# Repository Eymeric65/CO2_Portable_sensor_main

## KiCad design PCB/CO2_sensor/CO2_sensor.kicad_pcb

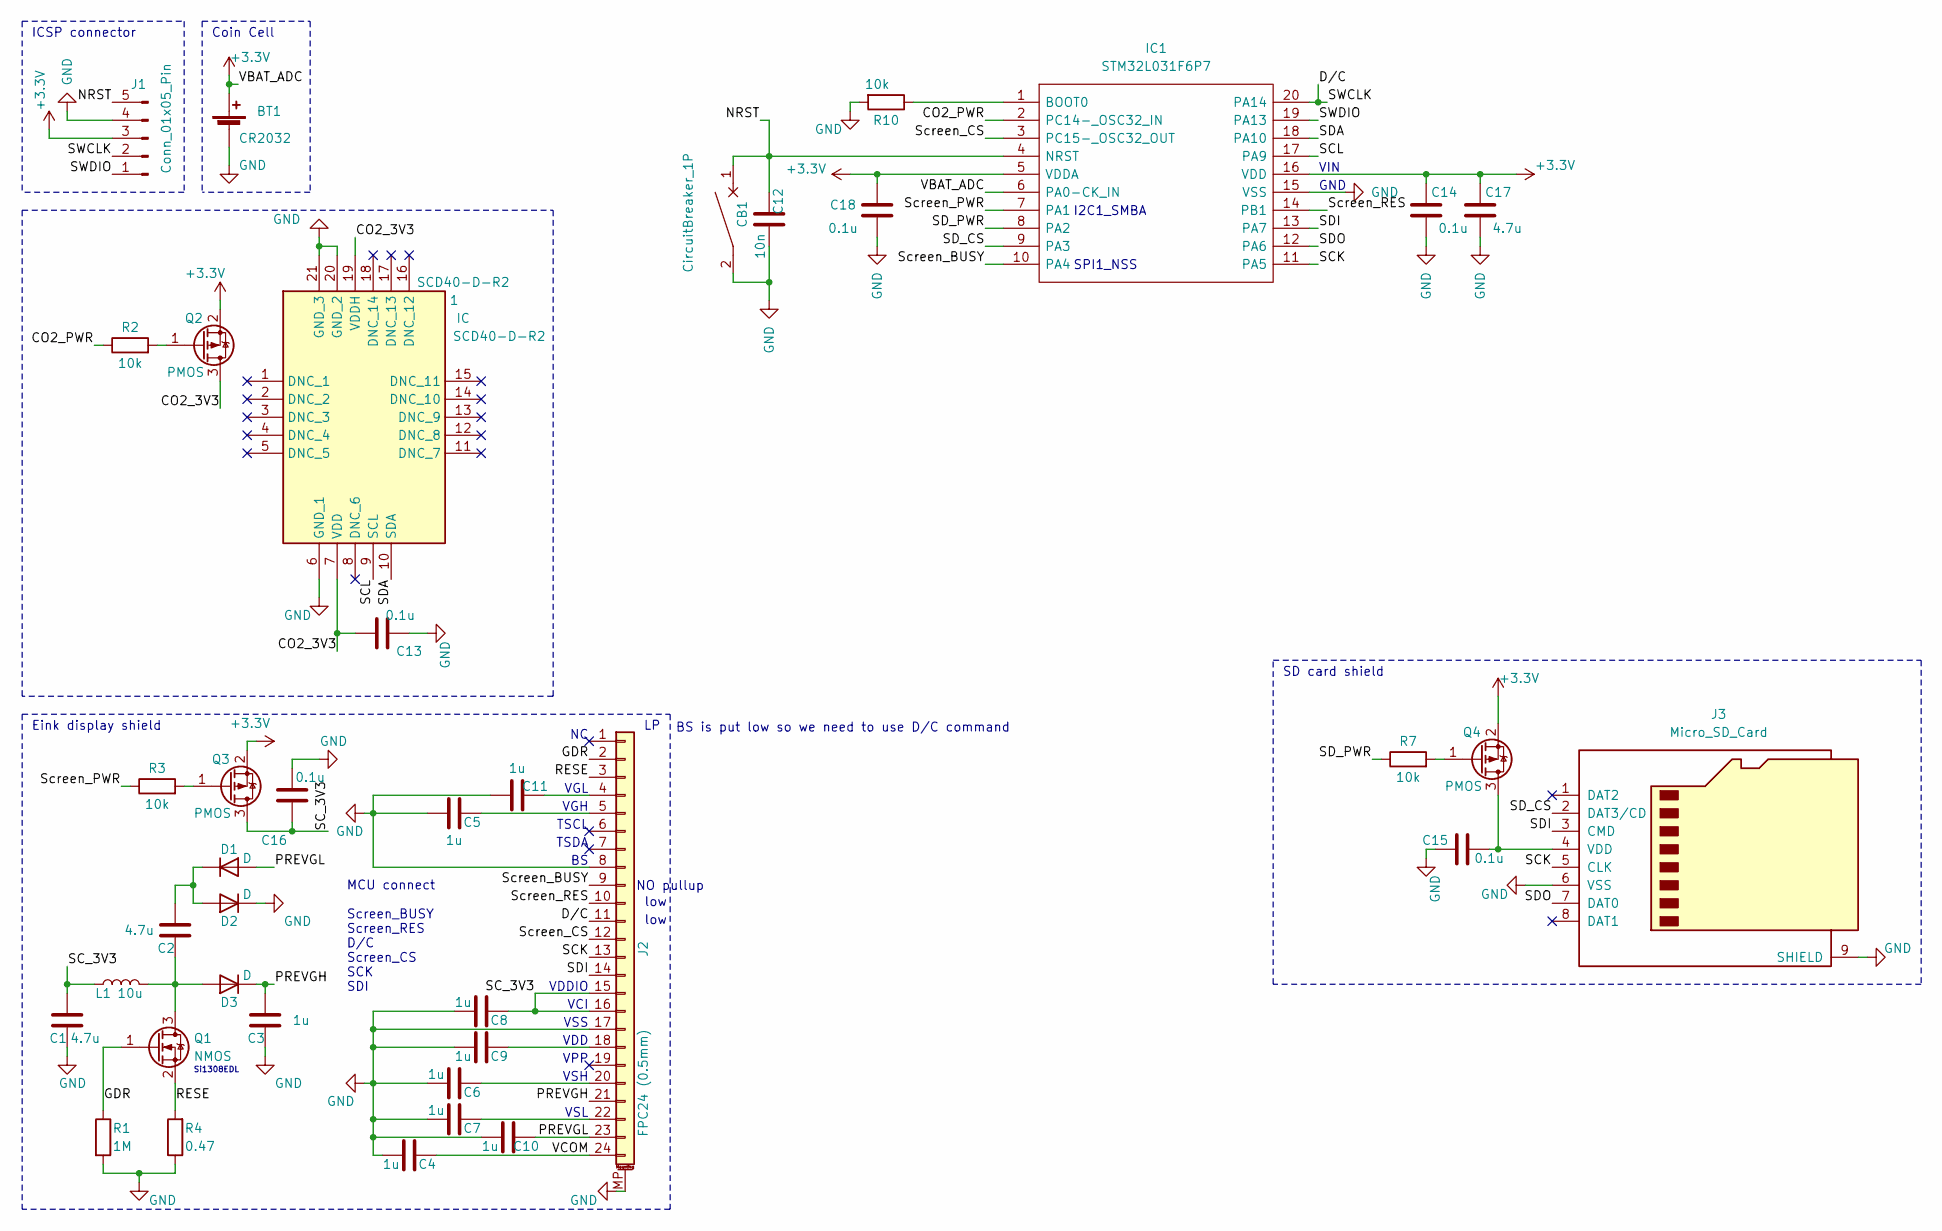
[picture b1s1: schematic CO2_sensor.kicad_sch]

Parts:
1: SCD40-D-R2; SCD40DR2; Manufacturer_Part_Number SCD40-D-R2; Mouser Part Number 403-SCD40-D-R2
BT1: CR2032; SMTM1225
C1, C2, C17: 4.7u; C_0603_1608Metric
C3, C4, C5, C6, C7, C8, C9, C10, C11: 1u; C_0603_1608Metric
C12: 10n; C_0603_1608Metric
C13, C14, C15, C16, C18: 0.1u; C_0603_1608Metric
CB1: CircuitBreaker_1P; TL3780AF240QG
D1, D2, D3: D; D_SOD-123
IC1: STM32L031F6P7; SOP65P640X120-20N; Mouser Part Number 511-STM32L031F6P7
J1: Conn_01x05_Pin; PinHeader_1x05_P2.00mm_Vertical
J2: FPC24 (0.5mm); TE_2-1734839-4_1x24-1MP_P0.5mm_Horizontal
J3: Micro_SD_Card; MSD1A
L1: 10u; SRN3015
Q1: NMOS; SOT-23
Q2, Q3, Q4: PMOS; SOT-23
R1: 1M; R_0603_1608Metric
R2, R3, R7, R10: 10k; R_0603_1608Metric
R4: 0.47; R_0603_1608Metric

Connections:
+3.3V: BT1.1 (+), C14.2, C17.2, C18.2, IC1.5 (VDDA), IC1.6 (PA0-CK_IN), IC1.16 (VDD), J1.3, Q2.2 (S), Q3.2 (S), Q4.2 (S)
/CO2_3V3: 1.7 (VDD), 1.19 (VDDH), C13.1, Q2.3 (D)
/CO2_PWR: IC1.2 (PC14-_OSC32_IN), R2.1
/D/C: IC1.20 (PA14), J1.2, J2.11
/GDR: J2.2, Q1.1 (G), R1.1
/NRST: C12.2, CB1.1, IC1.4 (NRST), J1.5
/PREVGH: C3.1, D3.1 (K), J2.21
/PREVGL: C10.2, D1.2 (A), J2.23
/RESE: J2.3, Q1.2 (S), R4.2
/SCK: IC1.11 (PA5), J2.13, J3.5 (CLK)
/SCL: 1.9 (SCL), IC1.17 (PA9)
/SC_3V3: C1.1, C8.2, C16.2, J2.15, J2.16, L1.1, Q3.3 (D)
/SDA: 1.10 (SDA), IC1.18 (PA10)
/SDI: IC1.13 (PA7), J2.14, J3.3 (CMD)
/SDO: IC1.12 (PA6), J3.7 (DAT0)
/SD_CS: IC1.9 (PA3), J3.2 (DAT3/CD)
/SD_PWR: IC1.8 (PA2), R7.1
/SWDIO: IC1.19 (PA13), J1.1
/Screen_BUSY: IC1.10 (PA4), J2.9
/Screen_CS: IC1.3 (PC15-_OSC32_OUT), J2.12
/Screen_PWR: IC1.7 (PA1), R3.1
/Screen_RES: IC1.14 (PB1), J2.10
/VCOM: C4.2, J2.24
GND: 1.6 (GND_1), 1.20 (GND_2), 1.21 (GND_3), BT1.2 (-), C1.2, C3.2, C4.1, C5.1, C6.1, C7.1, C8.1, C9.1, C10.1, C11.1, C12.1, C13.2, C14.1, C15.2, C16.1, C17.1, C18.1, CB1.2, D2.1 (K), IC1.15 (VSS), J1.4, J2.8, J2.17, J2.MP (MountPin), J3.6 (VSS), J3.9 (SHIELD), R1.2, R4.1, R10.2
unnamed: C2.1, D1.1 (K), D2.2 (A)
unnamed: C2.2, D3.2 (A), L1.2, Q1.3 (D)
unnamed: IC1.1 (BOOT0), R10.1
unnamed: C11.2, J2.4
unnamed: C5.2, J2.5
unnamed: C9.2, J2.18
unnamed: C6.2, J2.20
unnamed: C7.2, J2.22
unnamed: C15.1, J3.4 (VDD), Q4.3 (D)
unnamed: Q2.1 (G), R2.2
unnamed: Q3.1 (G), R3.2
unnamed: Q4.1 (G), R7.2

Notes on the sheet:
SD card shield
Si1308EDL
ICSP connector
VGH
SPI1_NSS
VSS
TSDA
VDD
BS is put low so we need to use D/C command
NO pullup
MCU connect Screen_BUSY Screen_RES D/C Screen_CS SCK SDI
TSCL
VPP
VIN
GND
low
VDDIO
VGL
Coin Cell
VCI
Eink display shield
VSH
I2C1_SMBA
VSL

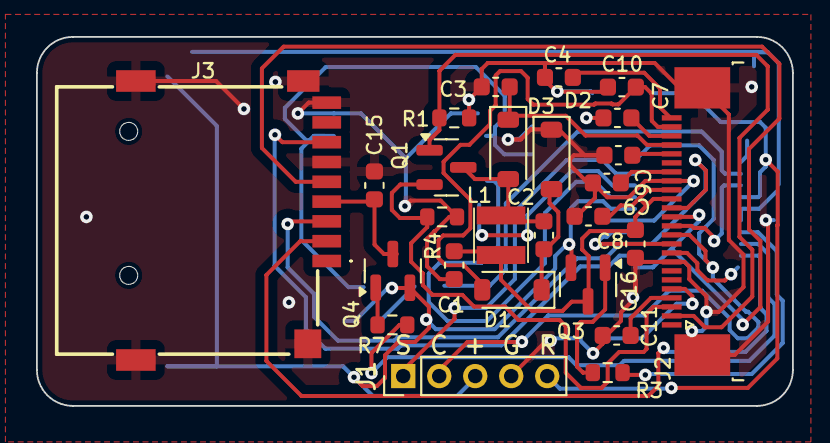
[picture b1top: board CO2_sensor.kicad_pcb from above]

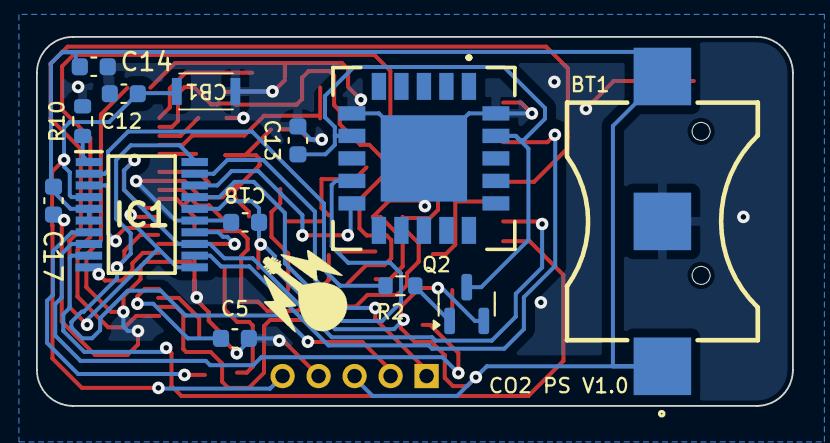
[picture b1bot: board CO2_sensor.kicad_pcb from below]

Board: 2 copper layers, 42.0 x 20.5 mm, 40 parts (14 on the bottom side), 36 nets.

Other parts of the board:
Ref**: Val**; drawing

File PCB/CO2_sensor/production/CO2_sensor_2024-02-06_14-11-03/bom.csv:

Designator,Footprint,Quantity,Value,LCSC Part #
1,SCD40DR2,1,SCD40-D-R2,
BT1,SMTM1225,1,CR2032,
"C1, C2",0603,2,4.7u,
"C10, C11, C3, C4, C5, C6, C7, C8, C9",0603,9,1u,
C12,0603,1,10n,
"C13, C14, C15, C16",0603,4,0.1u,
CB1,TL3780AF240QG,1,CircuitBreaker_1P,
"D1, D2, D3",D_SOD-123,3,D,
J1,PinHeader_1x05_P1.00mm_Vertical,1,Conn_01x05_Pin,
J2,Hirose_FH12-24S-0.5SH_1x24-1MP_P0.50mm_Horizontal,1,FPC24 (0.5mm),
J3,MSD1A,1,Micro_SD_Card,
L1,SRN3015,1,10u,
Q1,SOT-23,1,NMOS,
"Q2, Q3, Q4",SOT-23,3,PMOS,
R1,0603,1,1M,
"R2, R3, R5, R7, R8, R9",0603,6,10k,
R4,0603,1,0.47,
R6,0603,1,300,
U1,SSOP28_SS_MCH,1,PIC16F18155-I_SS,

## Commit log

2024-08-28 Settle everything
